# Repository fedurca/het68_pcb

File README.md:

# het68_pcb

Zadání a KiCad návrh PCB pro **het68** (akustická detekce dronů).

Co ještě zbývá před zadáním do výroby, včetně testovatelnosti a odolnosti proti rušení: [problems.md](problems.md).

Aktuální verze: **[v7.4.3](https://github.com/fedurca/het68_pcb/releases/tag/v7.4.3)** — viz [CHANGELOG.md](CHANGELOG.md). Kusovník sady: [kicad/BOM_KIT.csv](kicad/BOM_KIT.csv). Po deskách: [kicad/BOM_v4.csv](kicad/BOM_v4.csv).

Firmware a geometrie pole: [fedurca/het68](https://github.com/fedurca/het68). Zadání: [docs/ZADANI_PCB.md](docs/ZADANI_PCB.md). Projekty v KiCadu: [kicad/README.md](kicad/README.md).

## Co to je

v4 je sada **Core 8L + vyměnitelná silová deska + šest satelitů**. Na měď nepřijde 230 V, 22 kV ani 110 kV.

**Core** (`kicad/het68-core`) nese nativní RP2350B, flash, PSRAM, USB-C, šest RJ45 s LVDS, piezo, env senzor, stavovou SK6812 na 5 V, tlačítka RESET / BOOT / USER a `J_MESH` na Heltec WiFi LoRa 32 V3 (868 MHz). Akcelerometr na desce není. MeshCore běží na Heltecu, takže uzel v síti žije, i když DSP spí. `WAKE_DSP` zapíná `+3V3_DIG`.

**Silová deska** má tři SKU se stejným interconnectem 2×10: NN (multiplex CT), VN (silnější GDT/TVS), VVN (harvest CT + Rogowski). Společný front-end je jen sekundár: GDT, TVS, LC, burden, crowbar, MPPT, článek 21700 (LiFePO4/LTO), 5 V a vždyživý `+3V3_RF`.

**Satelit** je šest čtverců 52 × 52 mm, 8L. Mikrofon je uprostřed, kolem něj kruh **8× SK6812**. Svislý RJ45 a konfigurační propojky jsou na zadní straně co nejblíž středu. Režim linky volí propojka: diferenciální LVDS, jednostranných 3,3 V, nebo 1,8 V přímo na T5848. Význam propojek a postup osazení: [docs/SATELIT.md](docs/SATELIT.md). Mapa [`docs/PINOUT_SAT_v4.csv`](docs/PINOUT_SAT_v4.csv).

## Prototyp

Náhled satelitu je z v7.4.2. Core a silová deska mají stejnou měď jako ve v7.3.0.

Měď: [Core](docs/img/v740/core-top.svg) · [satelit ven](docs/img/v742/sat-front.svg) · [satelit zadek](docs/img/v742/sat-back.svg) · [silová](docs/img/v740/pwr-nn-top.svg). Maska venkovní strany satelitu: [SVG](docs/img/v742/sat-front-mask.svg). Schémata: [Core](docs/img/v740/core-sch.pdf) · [satelit](docs/img/v740/sat-sch.pdf) · [silová](docs/img/v740/pwr-nn-sch.pdf). Gerbery a nastavení formuláře: [`kicad/jlc/`](kicad/jlc/) · [NASTAVENI.md](kicad/jlc/NASTAVENI.md).

## Vyrobitelnost

Na měď nejde 230 V / 22 kV / 110 kV. Gerbery z `kicad-cli` v `kicad/*/fab/`. TPV: JLC / standardní výroba, ENIG na 6L a 8L, ≥ 0603, ne BGA. QFN-80 0,4 mm a LGA chtějí ENIG.

| Deska | Rozměr | ERC error | DRC | Objednat? |
|---|---|---|---|---|
| Core | 160 × 100 mm, 8L Faraday, ENIG | 0 | 0 zkratů, 0 mezer, 0 otevřených párů | měď ano; stroj osadí 111 součástek, dva LVDS přijímače ručně |
| Satelit | 52 × 52 mm, 8L, ven jen LED | 0 | 0 zkratů, 0 mezer, 0 otevřených párů | měď ano |
| Silová NN/VN/VVN | 140 × 80 mm, 6L, vnější měď 2 oz pokud kalkulace umí | 0 | 0 zkratů, 0 mezer, 0 otevřených párů | měď ano; stroj osadí 49 / 50 / 48 součástek z horní strany |

Schémata jsou elektricky uzavřená (ERC 0 chyb). Core je 8vrstvá: mezi GND_L5 a GND_L7 je SIG_L6 pro páry LVDS. Prokov je 0,30/0,15 mm. Satelit je čtverec 52 mm, 8 vrstev, prokov 0,60/0,20 mm. Mikrofon je ve středu, RJ45 a režimové propojky jsou na zadní straně hned u něj. Signálové sítě jsou spojené, delší spoje jdou po SIG_L6. Silové desky jsou 6vrstvé: F.Cu / GND_L2 / SIG_L3 / SIG_L4 / GND_L5 / B.Cu. Silové stopy jsou na vnější mědi, I2C a sense na vnitřní vrstvě. Stitch prokov je 1,00/0,50 mm, únik z jemného rastru 0,80/0,40 mm.

## VF / EMC (silné rušení)

- Core je 8L Faraday: L2, L5 a L7 jsou souvislá GND, L4 je plocha `+3V3_DIG` a nese i několik signálů, které mezi prokovy QFN jinde neprošly. L6 je signál mezi dvěma zeměmi. Zem je prošitá po obvodu s roztečí 1,5 mm. Satelit je 8L se stejným principem: SIG_L6 leží mezi GND_L5 a GND_L7. Silová deska je 6L, sense a I2C jdou mezi GND_L2 a GND_L5.
- Diferenciální režim vozí I²S po LVDS (T568B páry). Propojka na satelitu umí i jednostranných 3,3 V a 1,8 V. Stínění je na GND na Core i na satelitu.
- CMC na SCK, WS i SD na obou koncích; nízko-kapacitní TVS napříč párem; 100 Ω u přijímače (SN65LVDS2 / SN65LVDS32 nemají vnitřní zakončení).
- Ferit 600 Ω na 3V3 každého jacku a na satelitu za PPTC.
- Krystal 12 MHz s C0G 15 pF (ne X7R 100 nF). Sériové 33 Ω na I²S u MCU, 22 Ω + ESD na UART MeshCore.
- Rádio (SX1262) je na Heltecu mimo DSP; `+3V3_RF` je vždyživé a oddělené od hradlovaného `+3V3_DIG`.

## Co je ještě potřeba

1. **Firmware.** DSP = RP2350B. MeshCore na Heltecu: `Heltec_lora32_v3`, UART GPIO5/6, WAKE GPIO7.
2. **Core je uzavřené.** QFN, LVDS i silová deska mají měď dotaženou. Osazení silové desky a satelitu čeká na katalogové LCSC, kódy se nedoplňují odhadem.
3. **Heltec je lab.** ~40–80 mA. Stamp nRF52 později. LTO povinná, minimální SOC repeateru 30 %.
4. **110 kV.** Žádný externí kabel ze sféry. Anténa U.FL do slotu u stampu.
5. **RGB na 3,3 V.** Firmware svítí nejvýš dvěma pixely naráz.

## Sestava

Kleště / CT jsou na jednom izolovaném vodiči. Na desku jde jen sekundár (burden, LC, crowbar). Panel a článek LiFePO4/LTO jsou u silové desky, výstup `+5V_ALWAYS` jde na Core, šest satelitů je na RJ45.

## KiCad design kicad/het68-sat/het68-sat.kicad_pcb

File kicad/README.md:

# het68 — KiCad (v4.1.0)

Náhledy a kontext: [README](../README.md) repozitáře.

v4 kreslí **Core 8L**, tři silové SKU a satelit LVDS.

| Projekt | Deska | Vrstvy | Obrys |
|---|---|---|---|
| [het68-core](het68-core/het68-core.kicad_pro) | RP2350B + J_MESH Heltec V3 + 6× RJ45 LVDS | 8 Faraday | 160 × 100 mm |
| [het68-sat](het68-sat/het68-sat.kicad_pro) | satelit 8L LVDS + T5848 + 8× SK6812 | 8, ENIG | 52 × 52 mm |
| [het68-pwr-nn](het68-pwr-nn/het68-pwr-nn.kicad_pro) | silová NN, multiplex CT | 6, vnější 2 oz pokud kalkulace umí | 140 × 80 mm |
| [het68-pwr-vn](het68-pwr-vn/het68-pwr-vn.kicad_pro) | silová VN, 15KP | 6, stejně jako NN | 140 × 80 mm |
| [het68-pwr-vvn](het68-pwr-vvn/het68-pwr-vvn.kicad_pro) | silová VVN, Rogowski | 6, stejně jako NN | 140 × 80 mm |

Generátor: `kicad/tools/gen_v4.py` (Python z KiCadu). 6L stackup: `kicad/tools/route6.py`. Kusovník sady: [`BOM_KIT.csv`](BOM_KIT.csv).

## Zapojení Core

- RP2350B QFN-80, W25Q128 SOIC-8, APS6404L SOIC-8, USB-C, krystal 12 MHz + C0G 15 pF.
- `+3V3_DIG` a `+1V8_AUDIO` hradluje `WAKE_DSP` (Heltec GPIO7). `+5V_ALWAYS` / `+3V3_RF` vždyživé.
- `J_MESH` 1×8: GND, 5V, UART TX/RX (22 Ω + ESD), WAKE_DSP, DSP_AWAKE, RST NC, rezerva. Stamp DNP paralelně na pinech 1–6.
- Šest svislých RJ45, zástrčka kolmo z přední strany. Mapa [`docs/PINOUT_SAT_v4.csv`](../docs/PINOUT_SAT_v4.csv). CMC na SCK/WS/SD, 100 Ω u RX SD, ferit na 3V3.
- GPIO: [`docs/PINOUT.csv`](../docs/PINOUT.csv).
- Interconnect: [`docs/INTERCONNECT_v4.md`](../docs/INTERCONNECT_v4.md).
- L1 SMT+GND, L2 GND, L3 stripline, L4 souvislá `+3V3_DIG`, L5 GND, L6 pomalé+GND. Prokov 0,30/0,15 mm. Stitch po obvodu.

## Silová deska

Jen sekundár CT/Rogowski. GDT, TVS, LC, THT burden 100 Ω, crowbar ~25 V, USB-C lab, CN3791, LiFePO4, boost 5 V, LDO 3V3_RF, INA3221, PT1000. NN má MOSFET multiplex burdenu. VN 15KP. VVN Rogowski + MCP6001.

## Satelit

Deska je čtverec 52 × 52 mm, 8 vrstev. RJ45 stojí ze zadní strany, osa zástrčky je kolmá k desce, tělo je hned u mikrofonu. Režim linky volí jedna vodorovná propojka na 2×3. Pin 1 je severovýchodní. Severní řádek je diferenciální LVDS, prostřední je 3,3 V přes `TXS0104E`, jižní je 1,8 V přímo na T5848. Tabulka a postup osazení jsou v [docs/SATELIT.md](../docs/SATELIT.md). T5848 zůstává na 1,62–1,98 V. Stínění RJ45 je na GND. DRC satelitu je 0 zkratů, 0 mezer a 0 otevřených párů. Náhled s tělem mikrofonu je v [`docs/img/v742/`](../docs/img/v742/). ENIG, ≥ 0603.

## Výroba

Gerbery z `kicad-cli pcb export gerbers` (ne `WriteDRCReport`). Core je 8L ENIG, satelit 8L ENIG, silová deska 6L.

v4.1.0: schémata elektricky uzavřená, BoM sady, 3D náhledy. Spoje 6L jsou v4.2.0.

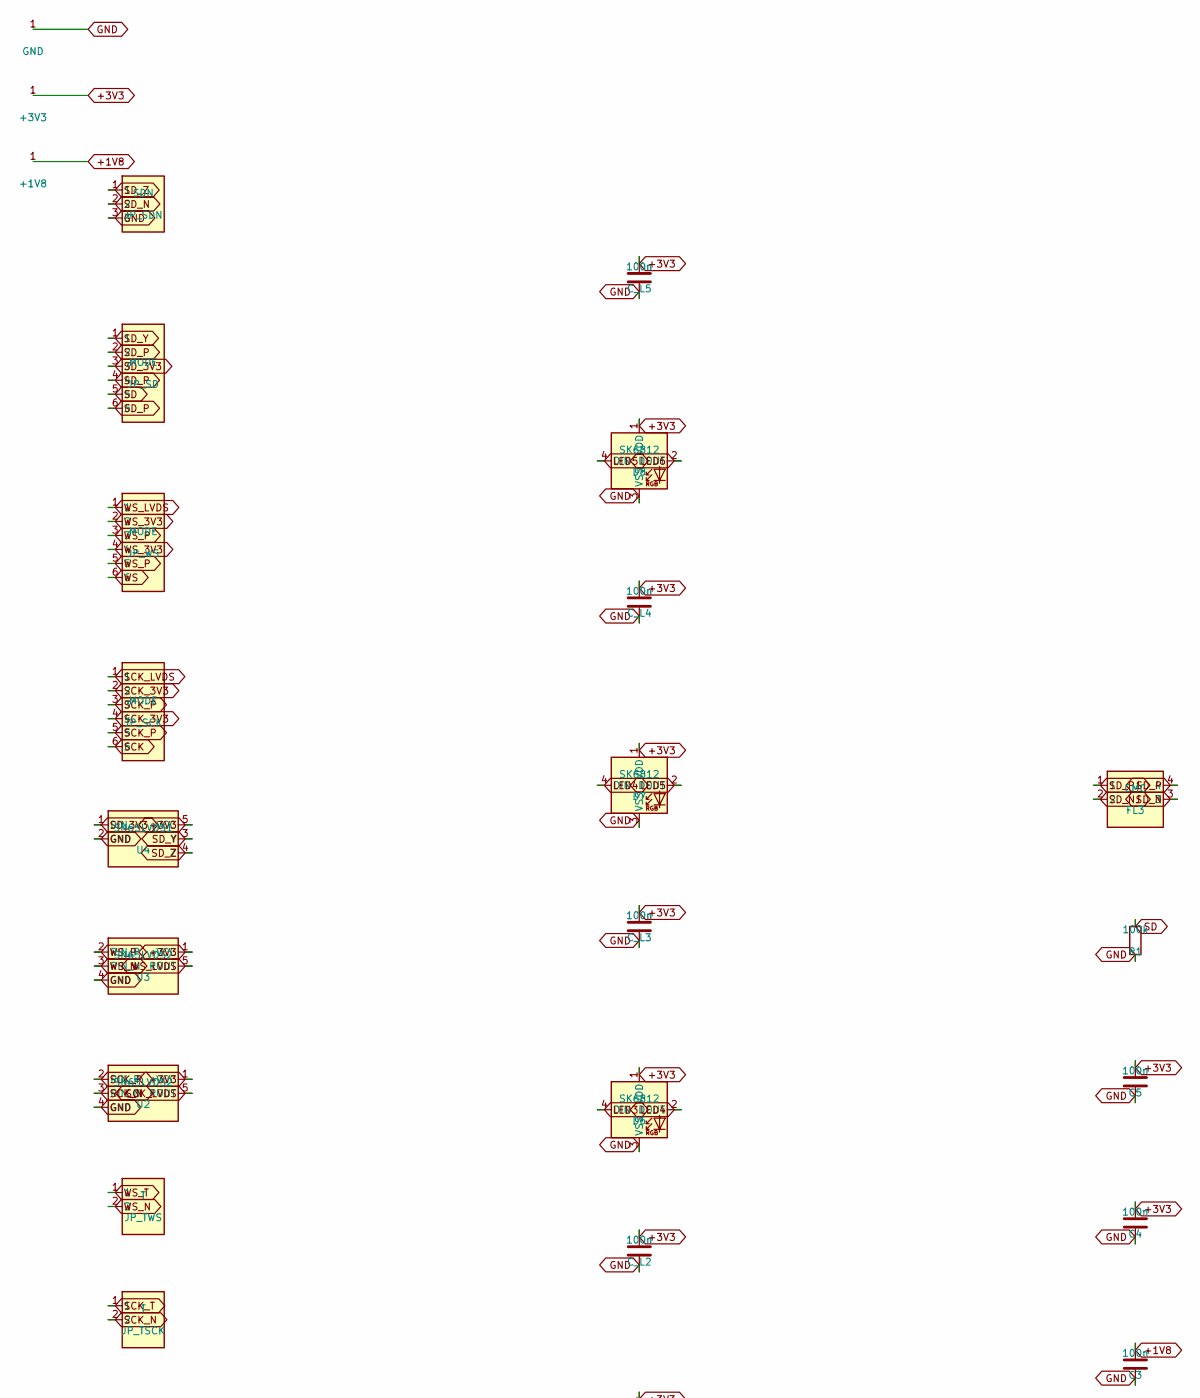
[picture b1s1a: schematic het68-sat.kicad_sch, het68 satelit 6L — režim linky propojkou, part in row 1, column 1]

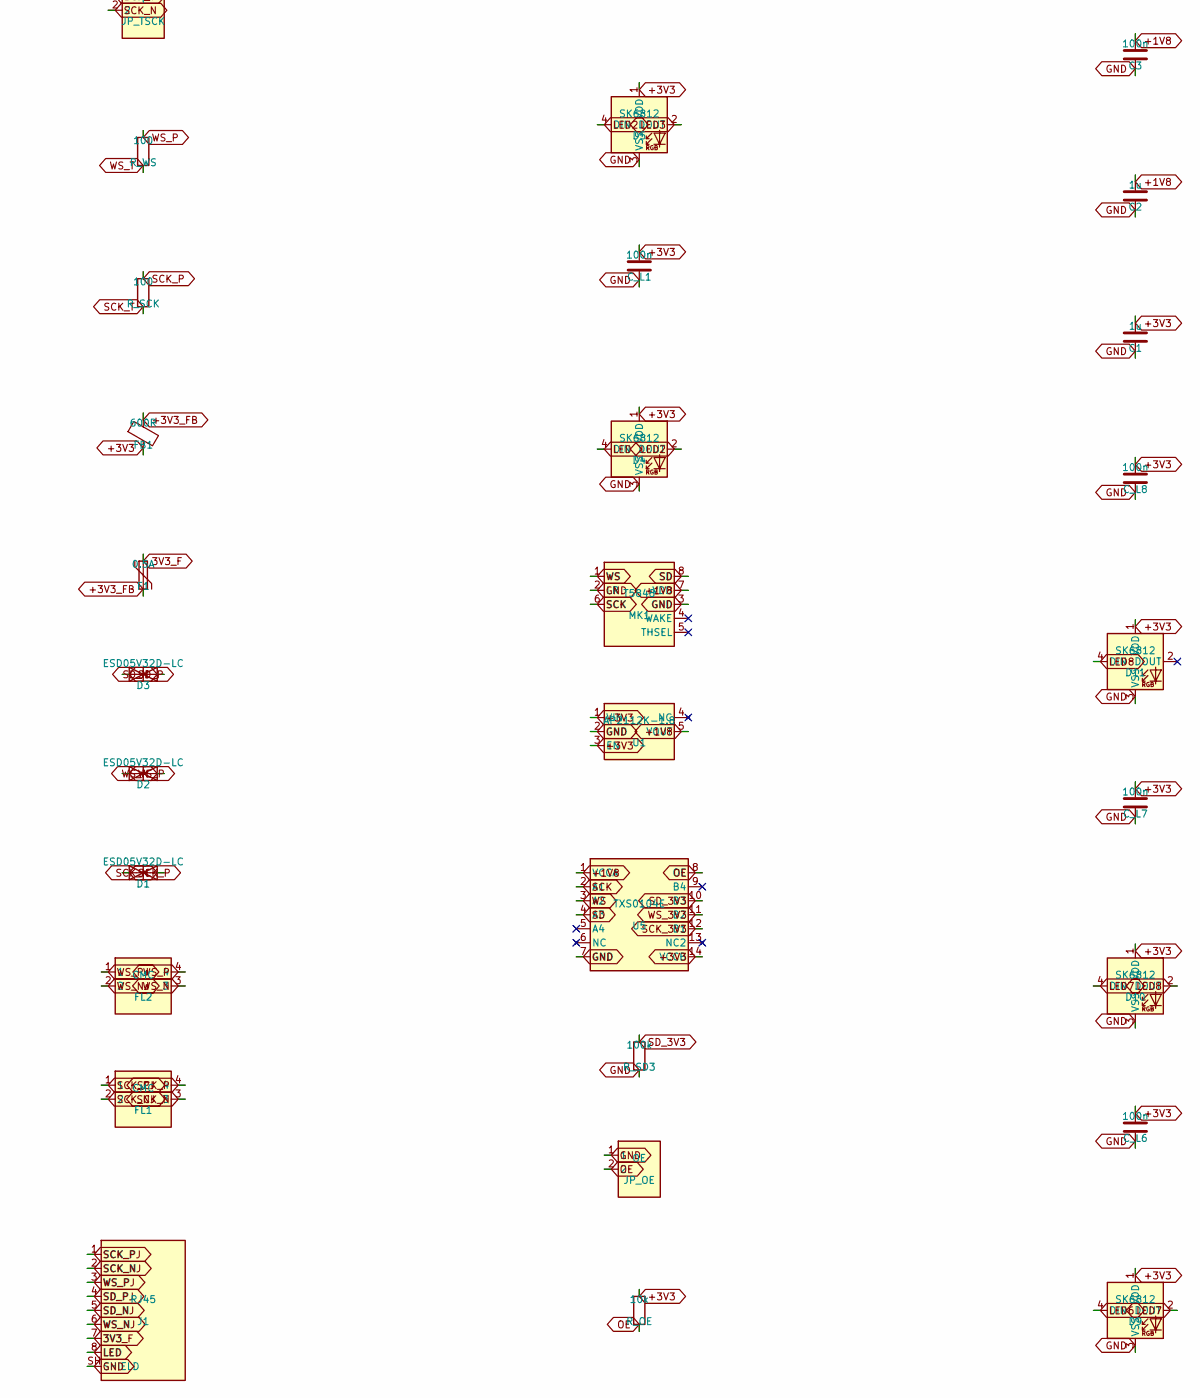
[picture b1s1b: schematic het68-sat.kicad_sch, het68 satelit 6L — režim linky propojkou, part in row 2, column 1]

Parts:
C1, C2: 1u; C_0603_1608Metric; MPN CL10A105KA8NNNC
C3, C4, C5: 100n; C_0603_1608Metric; MPN CL10B104KB8NNNC
C_L1, C_L2, C_L3, C_L4, C_L5, C_L6, C_L7, C_L8: 100n; C_0603_1608Metric; MPN CL10B104KB8NNNC
D1, D2, D3: ESD05V32D-LC; D_SOD-323; MPN ESD05V32D-LC
D4, D5, D6, D7, D8, D9, D10, D11: SK6812; LED_WS2812B_PLCC4_5.0x5.0mm_P3.2mm; MPN SK6812
F1: 0.5A; Fuse_0603_1608Metric; MPN 0603L050/6V
FB1: 600R; L_0603_1608Metric; MPN BLM18AG601SN1D
FL1, FL2, FL3: CMC; L_CommonModeChoke_Coilank_ACM2012; MPN ACM2012-900-2P-T001
J1: RJ45; RJ45_Vertical_het68; MPN RJ45-8P8C-VERT
JP_OE: OE; PinHeader_1x02_P2.54mm_Vertical; MPN jumper OE to GND = 1V8 mode
JP_SCK: MODE; PinHeader_2x03_P2.54mm_Vertical; MPN SCK radky DIFF / 3V3 / 1V8
JP_SD: MODE; PinHeader_2x03_P2.54mm_Vertical; MPN SD radky DIFF / 3V3 / 1V8
JP_SDN: SDN; PinHeader_1x03_P2.54mm_Vertical; MPN jumper SDN 1-2 DIFF 2-3 single-ended
JP_TSCK: T; PinHeader_1x02_P2.54mm_Vertical; MPN jumper DIFF term SCK
JP_TWS: T; PinHeader_1x02_P2.54mm_Vertical; MPN jumper DIFF term WS
JP_WS: MODE; PinHeader_2x03_P2.54mm_Vertical; MPN WS radky DIFF / 3V3 / 1V8
MK1: T5848; MPN MMICT5848-00-012
R1: 100k; R_0603_1608Metric; MPN RC0603FR-07100KL
R_OE: 10k; R_0603_1608Metric; MPN RC0603FR-0710KL
R_SCK: 100; R_0603_1608Metric; MPN RC0603FR-07100RL
R_SD3: 100k; R_0603_1608Metric; MPN RC0603FR-07100KL
R_WS: 100; R_0603_1608Metric; MPN RC0603FR-07100RL
U1: AP2112K-1.8; SOT-23-5; MPN AP2112K-1.8TRG1
U2, U3: SN65LVDS2; SOT-23-5; MPN SN65LVDS2DBVR
U4: SN65LVDS1; SOT-23-5; MPN SN65LVDS1DBVR
U5: TXS0104E; SOIC-14_3.9x8.7mm_P1.27mm; MPN TXS0104EDR

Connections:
3V3_F: F1.1, J1.7 (3V3)
+1V8: C2.1, C3.1, MK1.7 (VDD), U1.5 (VOUT), U5.1 (VCCA)
+3V3: C1.1, C4.1, C5.1, C_L1.1, C_L2.1, C_L3.1, C_L4.1, C_L5.1, C_L6.1, C_L7.1, C_L8.1, D4.1 (VDD), D5.1 (VDD), D6.1 (VDD), D7.1 (VDD), D8.1 (VDD), D9.1 (VDD), D10.1 (VDD), D11.1 (VDD), FB1.2, R_OE.1, U1.1 (VIN), U1.3 (EN), U2.1 (VCC), U3.1 (VCC), U4.5 (VCC), U5.14 (VCCB)
+3V3_FB: F1.2, FB1.1
GND: C1.2, C2.2, C3.2, C4.2, C5.2, C_L1.2, C_L2.2, C_L3.2, C_L4.2, C_L5.2, C_L6.2, C_L7.2, C_L8.2, D4.3 (VSS), D5.3 (VSS), D6.3 (VSS), D7.3 (VSS), D8.3 (VSS), D9.3 (VSS), D10.3 (VSS), D11.3 (VSS), J1.SH (SHIELD), JP_OE.1, JP_SDN.3, MK1.2 (LR), MK1.3 (GND), R1.2, R_SD3.2, U1.2 (GND), U2.4 (GND), U3.4 (GND), U4.2 (GND), U5.7 (GND)
LED: D4.4 (DIN), J1.8 (LED)
LED2: D4.2 (DOUT), D5.4 (DIN)
LED3: D5.2 (DOUT), D6.4 (DIN)
LED4: D6.2 (DOUT), D7.4 (DIN)
LED5: D7.2 (DOUT), D8.4 (DIN)
LED6: D8.2 (DOUT), D9.4 (DIN)
LED7: D9.2 (DOUT), D10.4 (DIN)
LED8: D10.2 (DOUT), D11.4 (DIN)
OE: JP_OE.2, R_OE.2, U5.8 (OE)
SCK: JP_SCK.6, MK1.6 (SCK), U5.2 (A1)
SCK_3V3: JP_SCK.2, JP_SCK.4, U5.12 (B1)
SCK_LVDS: JP_SCK.1, U2.5 (ROUT)
SCK_N: D1.2 (A2), FL1.3, JP_TSCK.2, U2.3 (RIN_N)
SCK_NJ: FL1.2, J1.2 (SCK_N)
SCK_P: D1.1 (A1), FL1.4, JP_SCK.3, JP_SCK.5, R_SCK.1, U2.2 (RIN_P)
SCK_PJ: FL1.1, J1.1 (SCK_P)
SCK_T: JP_TSCK.1, R_SCK.2
SD: JP_SD.5, MK1.8 (SD), R1.1, U5.4 (A3)
SD_3V3: JP_SD.3, R_SD3.1, U4.1 (DIN), U5.10 (B3)
SD_N: D3.2 (A2), FL3.3, JP_SDN.2
SD_NJ: FL3.2, J1.5 (SD_N)
SD_P: D3.1 (A1), FL3.4, JP_SD.2, JP_SD.4, JP_SD.6
SD_PJ: FL3.1, J1.4 (SD_P)
SD_Y: JP_SD.1, U4.3 (Y)
SD_Z: JP_SDN.1, U4.4 (Z)
WS: JP_WS.6, MK1.1 (WS), U5.3 (A2)
WS_3V3: JP_WS.2, JP_WS.4, U5.11 (B2)
WS_LVDS: JP_WS.1, U3.5 (ROUT)
WS_N: D2.2 (A2), FL2.3, JP_TWS.2, U3.3 (RIN_N)
WS_NJ: FL2.2, J1.6 (WS_N)
WS_P: D2.1 (A1), FL2.4, JP_WS.3, JP_WS.5, R_WS.1, U3.2 (RIN_P)
WS_PJ: FL2.1, J1.3 (WS_P)
WS_T: JP_TWS.1, R_WS.2

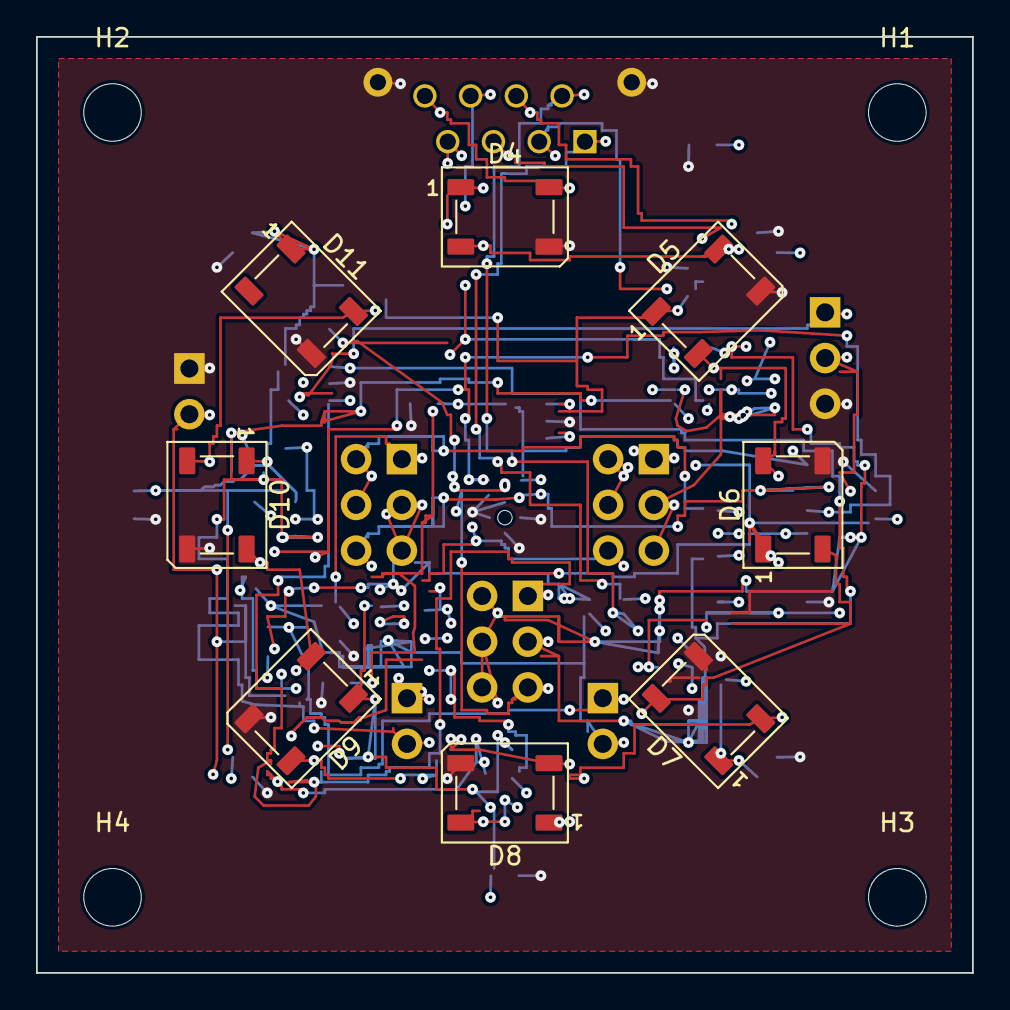
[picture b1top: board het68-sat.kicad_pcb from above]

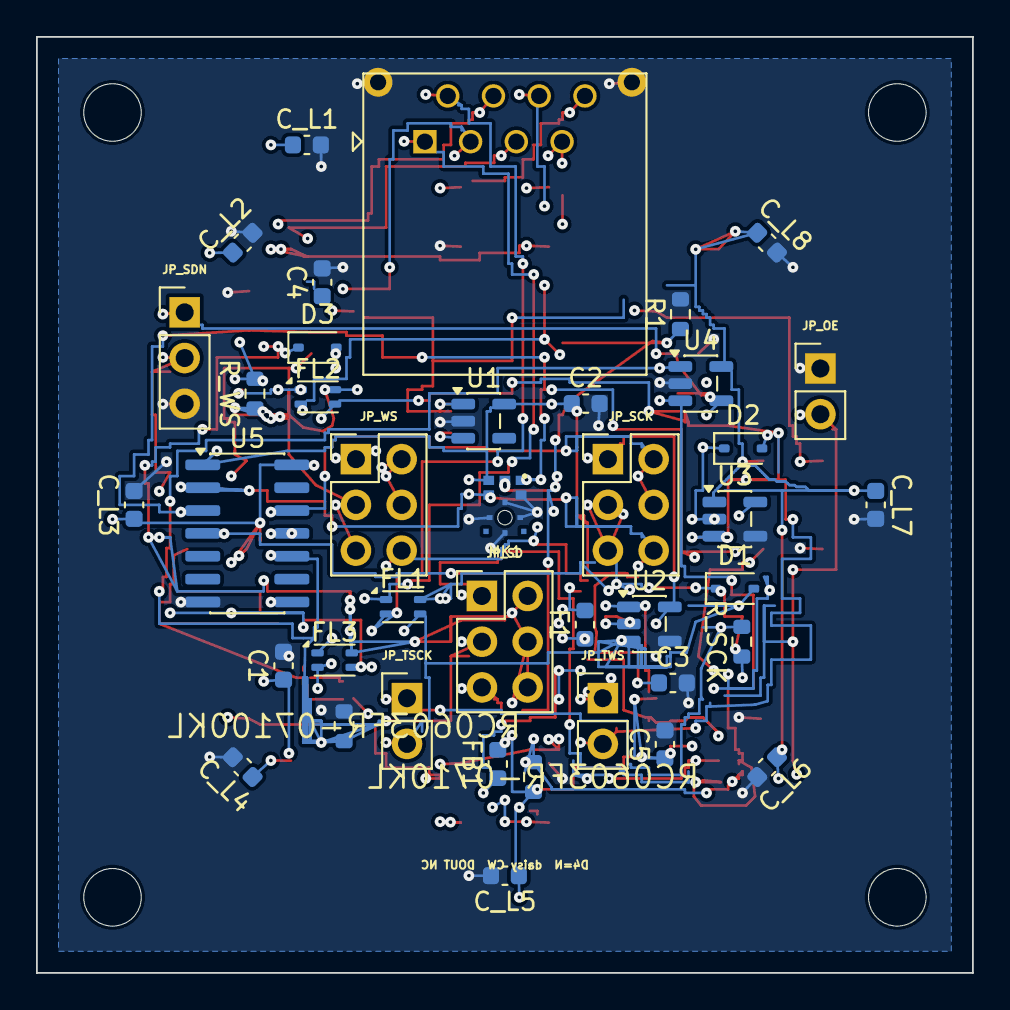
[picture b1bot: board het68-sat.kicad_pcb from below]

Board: 8 copper layers, 52.0 x 52.0 mm, 52 parts (40 on the bottom side), 38 nets.

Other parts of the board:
H1, H2, H3, H4: M3; MountingHole_3.2mm_M3

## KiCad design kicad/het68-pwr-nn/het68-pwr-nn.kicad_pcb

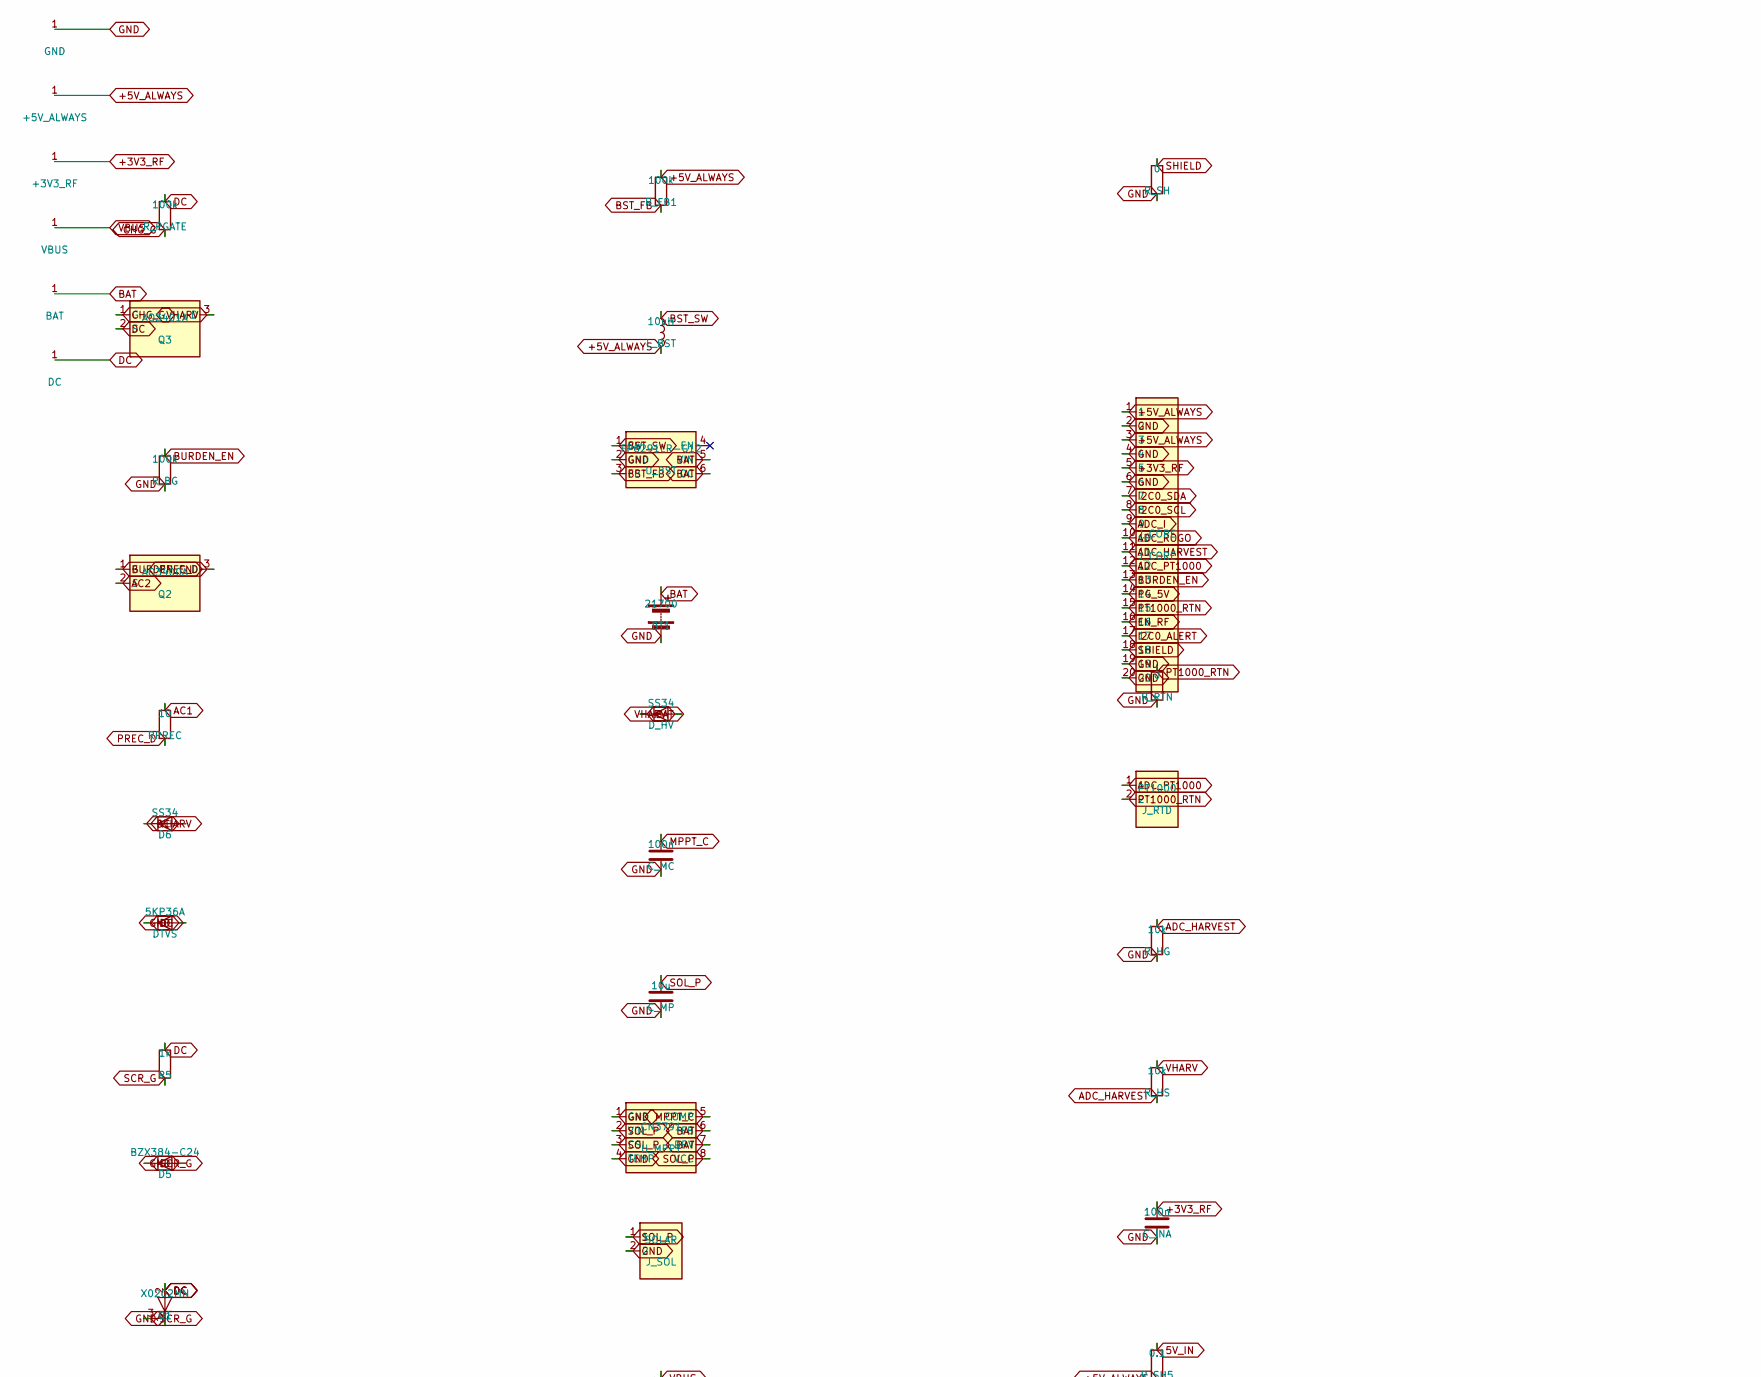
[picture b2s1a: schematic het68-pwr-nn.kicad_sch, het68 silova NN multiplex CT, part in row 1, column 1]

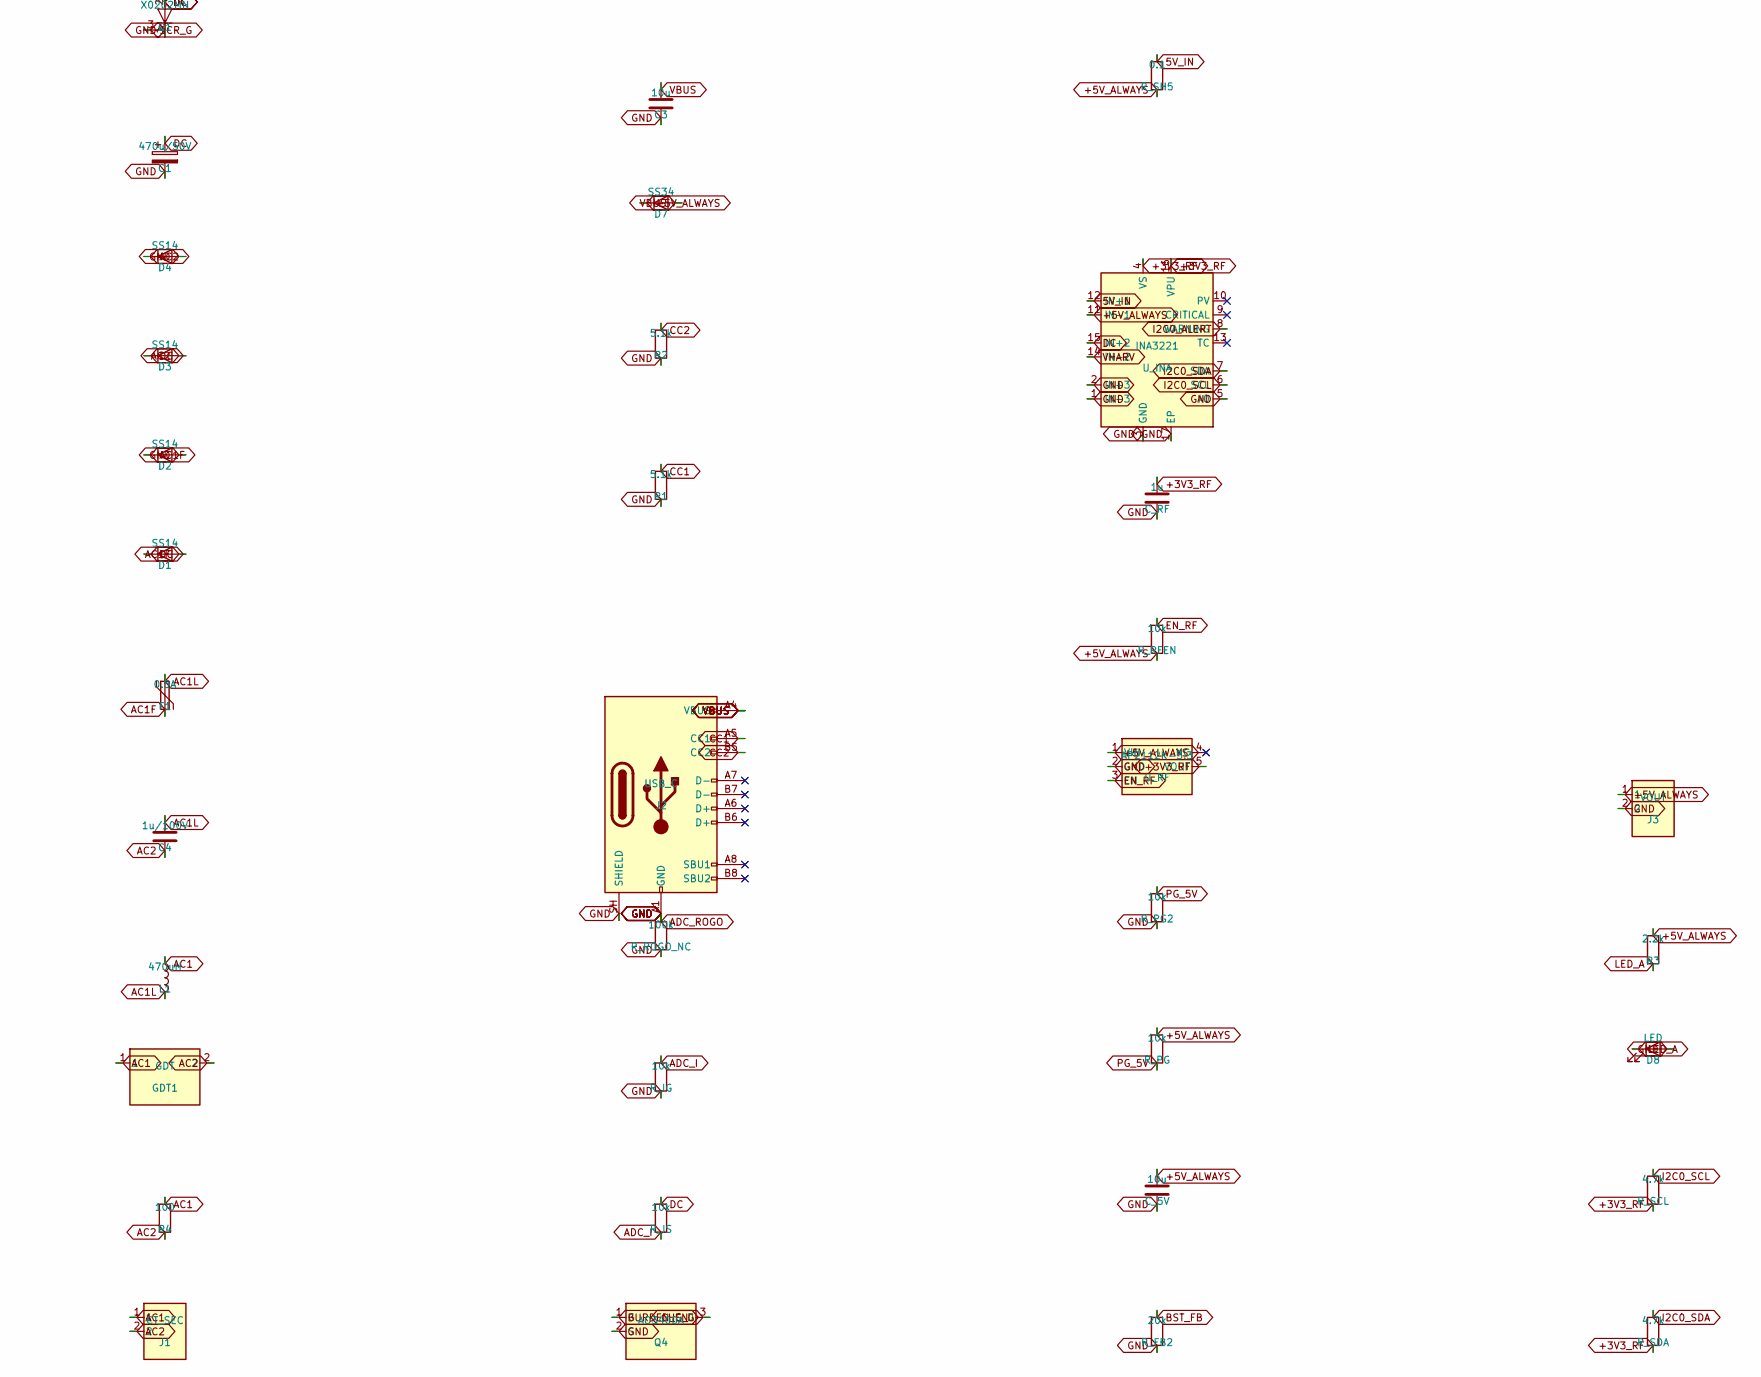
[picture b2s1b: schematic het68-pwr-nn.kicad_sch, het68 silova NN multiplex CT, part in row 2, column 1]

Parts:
BT1: 21700; Keystone_1122_21700; MPN Keystone 1122
C1: 470u/50V; CP_Radial_D10.0mm_P5.00mm; MPN electrolytic 470u 50V
C3: 10u; C_0805_2012Metric; MPN CL21A106KOQNNNE
C4: 1u/100V; C_1206_3216Metric; MPN CL31B105KCHNNNE
C_5V: 10u; C_0805_2012Metric; MPN CL21A106KOQNNNE
C_INA: 100n; C_0603_1608Metric; MPN CL10B104KB8NNNC
C_MC: 100n; C_0603_1608Metric; MPN CL10B104KB8NNNC
C_MP: 10u; C_0805_2012Metric; MPN CL21A106KOQNNNE
C_RF: 1u; C_0603_1608Metric; MPN CL10A105KA8NNNC
D1, D2, D3, D4: SS14; D_SMA; MPN SS14
D5: BZX384-C24; D_SOD-323; MPN BZX384-C24
D6, D7: SS34; D_SMC; MPN SS34
D8: LED; LED_0603_1608Metric; MPN KT-0603R
DTVS: 5KP36A; D_DO-201_P15.24mm_Horizontal; MPN 5KP36A
D_HV: SS34; D_SMC; MPN SS34
F1: 0.5A; Fuse_1812_4532Metric; MPN 1812L050PR
GDT1: GDT; Fuse_1812_4532Metric; MPN SMD4532-090NF
J1: CT_SEC; PinHeader_1x02_P2.54mm_Vertical; MPN sekundar CT, NE sit
J2: USB_C; USB_C_Receptacle_HRO_TYPE-C-31-M-12; MPN TYPE-C-31-M-12
J3: VOUT; PinHeader_1x02_P2.54mm_Vertical; MPN 5V lab
J_CORE: J_CORE; PinHeader_2x10_P2.54mm_Vertical; MPN interconnect 2x10
J_RTD: PT1000; PinHeader_1x02_P2.54mm_Vertical; MPN PT1000 on conductor
J_SOL: SOLAR; PinHeader_1x02_P2.54mm_Vertical; MPN panel Voc 6-18 V
L1: 470uH; L_Radial_D10.0mm_P5.00mm_Fastron_07P; MPN 470uH radial
L_BST: 10uH; L_0805_2012Metric; MPN MTQH201210S100MBT
Q1: X0202MN; SOT-223; MPN X0202MN 5BA4
Q2, Q4: AO3400A; SOT-23; MPN AO3400A
Q3: AO3401A; SOT-23; MPN AO3401A
R1, R2: 5.1k; R_0603_1608Metric; MPN RC0603FR-075K1L
R3: 2.2k; R_0603_1608Metric; MPN RC0603FR-072K2L
R4: 100; R_Axial_DIN0207_L6.3mm_D2.5mm_P10.16mm_Horizontal; MPN 100R THT burden
R5: 1k; R_0805_2012Metric; MPN RC0805FR-071KL
RPREC: 10; R_1206_3216Metric; MPN RT1206BRD0710RL
R_BG: 100k; R_0603_1608Metric; MPN RC0603FR-07100KL
R_FB1: 100k; R_0603_1608Metric; MPN RC0603FR-07100KL
R_FB2: 20k; R_0603_1608Metric; MPN RC0603FR-0720KL
R_HG: 10k; R_0603_1608Metric; MPN RC0603FR-0710KL
R_HS: 10k; R_0603_1608Metric; MPN RC0603FR-0710KL
R_IG: 10k; R_0603_1608Metric; MPN RC0603FR-0710KL
R_IS: 10k; R_0603_1608Metric; MPN RC0603FR-0710KL
R_PG, R_PG2: 10k; R_0603_1608Metric; MPN RC0603FR-0710KL
R_PGATE: 100k; R_0603_1608Metric; MPN RC0603FR-07100KL
R_RFEN: 10k; R_0603_1608Metric; MPN RC0603FR-0710KL
R_ROGO_NC: 100k; R_0603_1608Metric; MPN RC0603FR-07100KL
R_RTN: 0; R_0603_1608Metric; MPN RC0603FR-070RL
R_SCL: 4.7k; R_0603_1608Metric; MPN RC0603FR-074K7L
R_SDA: 4.7k; R_0603_1608Metric; MPN RC0603FR-074K7L
R_SH: 0; R_0603_1608Metric; MPN RC0603FR-070RL
R_SH5: 0.1; R_0805_2012Metric; MPN RTT05R100FTP
U_BST: FP6291LR-G12; SOT-23-6; MPN FP6291LR-G12
U_INA: INA3221; Texas_RGV0016A_VQFN-16-1EP_4x4mm_P0.65mm_EP2.1x2.1mm; MPN INA3221AIRGVR
U_MPPT: CN3791; SOIC-8_3.9x4.9mm_P1.27mm; MPN CN3791
U_RF: AP2112K-3.3; SOT-23-5; MPN AP2112K-3.3TRG1

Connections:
5V_IN: R_SH5.1, U_INA.12 (IN+1)
+3V3_RF: C_INA.1, C_RF.1, J_CORE.5, R_SCL.2, R_SDA.2, U_INA.4 (VS), U_INA.16 (VPU), U_RF.5 (VOUT)
+5V_ALWAYS: C_5V.1, D7.1 (K), J3.1, J_CORE.1, J_CORE.3, L_BST.2, R3.1, R_FB1.1, R_PG.1, R_RFEN.2, R_SH5.2, U_INA.11 (IN-1), U_RF.1 (VIN)
AC1: GDT1.1, J1.1, L1.1, R4.1, RPREC.1
AC1F: D1.2 (A), D2.1 (K), F1.2
AC1L: C4.1, F1.1, L1.2
AC2: C4.2, D3.2 (A), D4.1 (K), GDT1.2, J1.2, Q2.2 (S), R4.2
ADC_HARVEST: J_CORE.11, R_HG.1, R_HS.2
ADC_I: J_CORE.9, R_IG.1, R_IS.2
ADC_PT1000: J_CORE.12, J_RTD.1
ADC_ROGO: J_CORE.10, R_ROGO_NC.1
BAT: BT1.1 (+), D_HV.1 (K), U_BST.4 (EN), U_BST.5 (VIN), U_BST.6 (OC), U_MPPT.6 (FB), U_MPPT.7 (DRV)
BST_FB: R_FB1.2, R_FB2.1, U_BST.3 (FB)
BST_SW: L_BST.1, U_BST.1 (SW)
BURDEN_EN: J_CORE.13, Q2.1 (G), Q4.1 (G), R_BG.1
CC1: J2.A5 (CC1), R1.1
CC2: J2.B5 (CC2), R2.1
CHG_G: Q3.1 (G), Q4.3 (D), R_PGATE.2
DC: C1.1, D1.1 (K), D3.1 (K), D6.2 (A), DTVS.1 (K), Q1.2 (A), Q1.4 (A), Q3.2 (S), R5.1, R_IS.1, R_PGATE.1, U_INA.15 (IN+2)
EN_RF: J_CORE.16, R_RFEN.1, U_RF.3 (EN)
GND: BT1.2 (-), C1.2, C3.2, C_5V.2, C_INA.2, C_MC.2, C_MP.2, C_RF.2, D2.2 (A), D4.2 (A), D5.2 (A), D8.2 (A), DTVS.2 (A), J2.A1 (GND), J2.A12 (GND), J2.B1 (GND), J2.B12 (GND), J2.SH (SHIELD), J3.2, J_CORE.2, J_CORE.4, J_CORE.6, J_CORE.19, J_CORE.20, J_SOL.2, Q1.1 (K), Q4.2 (S), R1.2, R2.2, R_BG.2, R_FB2.2, R_HG.2, R_IG.2, R_PG2.2, R_ROGO_NC.2, R_RTN.2, R_SH.2, U_BST.2 (GND), U_INA.1 (IN-3), U_INA.2 (IN+3), U_INA.3 (GND), U_INA.5 (A0), U_INA.17 (EP), U_MPPT.1 (GND), U_MPPT.4 (TEMP), U_RF.2 (GND)
I2C0_ALERT: J_CORE.17, U_INA.8 (WARNING)
I2C0_SCL: J_CORE.8, R_SCL.1, U_INA.6 (SCL)
I2C0_SDA: J_CORE.7, R_SDA.1, U_INA.7 (SDA)
LED_A: D8.1 (K), R3.2
MPPT_C: C_MC.1, U_MPPT.5 (COMP)
PG_5V: J_CORE.14, R_PG.2, R_PG2.1
PREC_D: Q2.3 (D), RPREC.2
PT1000_RTN: J_CORE.15, J_RTD.2, R_RTN.1
SCR_G: D5.1 (K), Q1.3 (G), R5.2
SHIELD: J_CORE.18, R_SH.1
SOL_P: C_MP.1, J_SOL.1, U_MPPT.2 (VIN), U_MPPT.3 (CS), U_MPPT.8 (VCC)
VBUS: C3.1, D7.2 (A), J2.A4 (VBUS), J2.A9 (VBUS), J2.B4 (VBUS), J2.B9 (VBUS)
VHARV: D6.1 (K), D_HV.2 (A), Q3.3 (D), R_HS.1, U_INA.14 (IN-2)

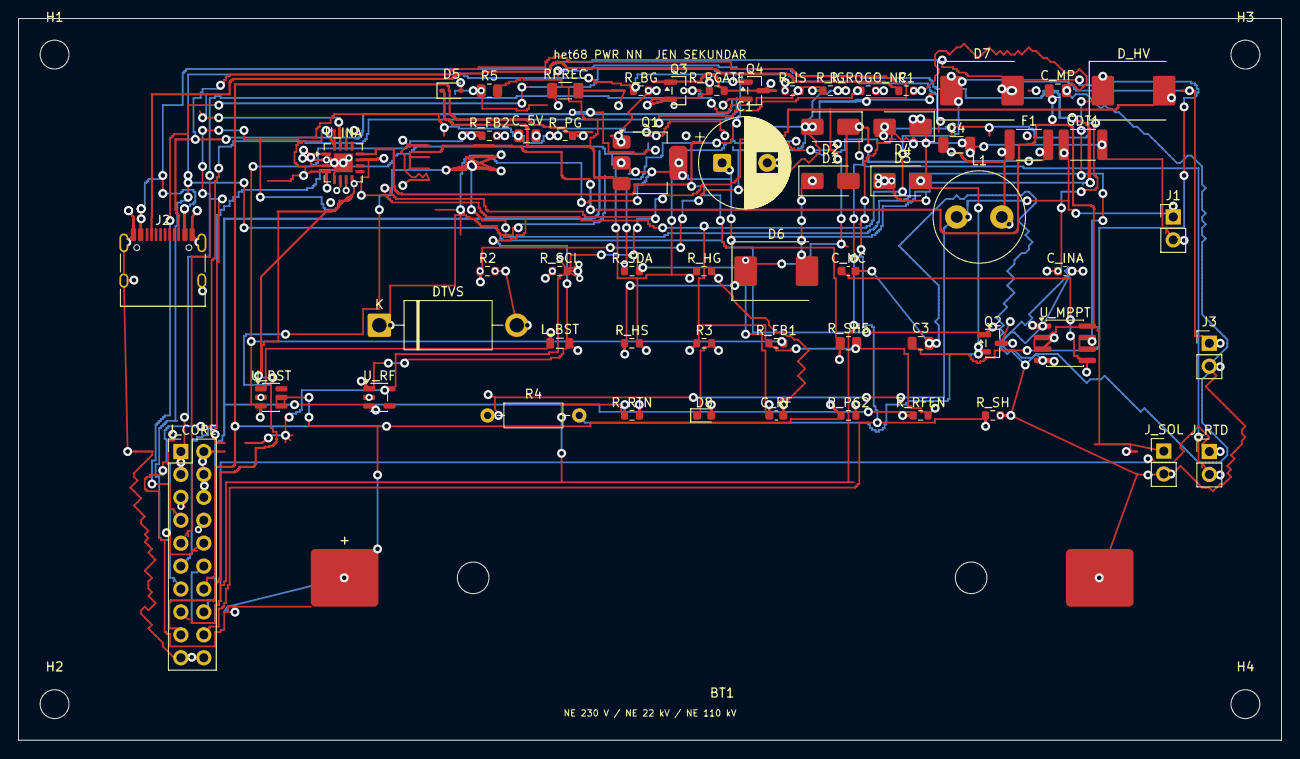
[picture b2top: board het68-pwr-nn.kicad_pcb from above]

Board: 6 copper layers, 140.0 x 80.0 mm, 64 parts (0 on the bottom side), 34 nets.

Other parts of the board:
H1, H2, H3, H4: M3; MountingHole_3.2mm_M3
